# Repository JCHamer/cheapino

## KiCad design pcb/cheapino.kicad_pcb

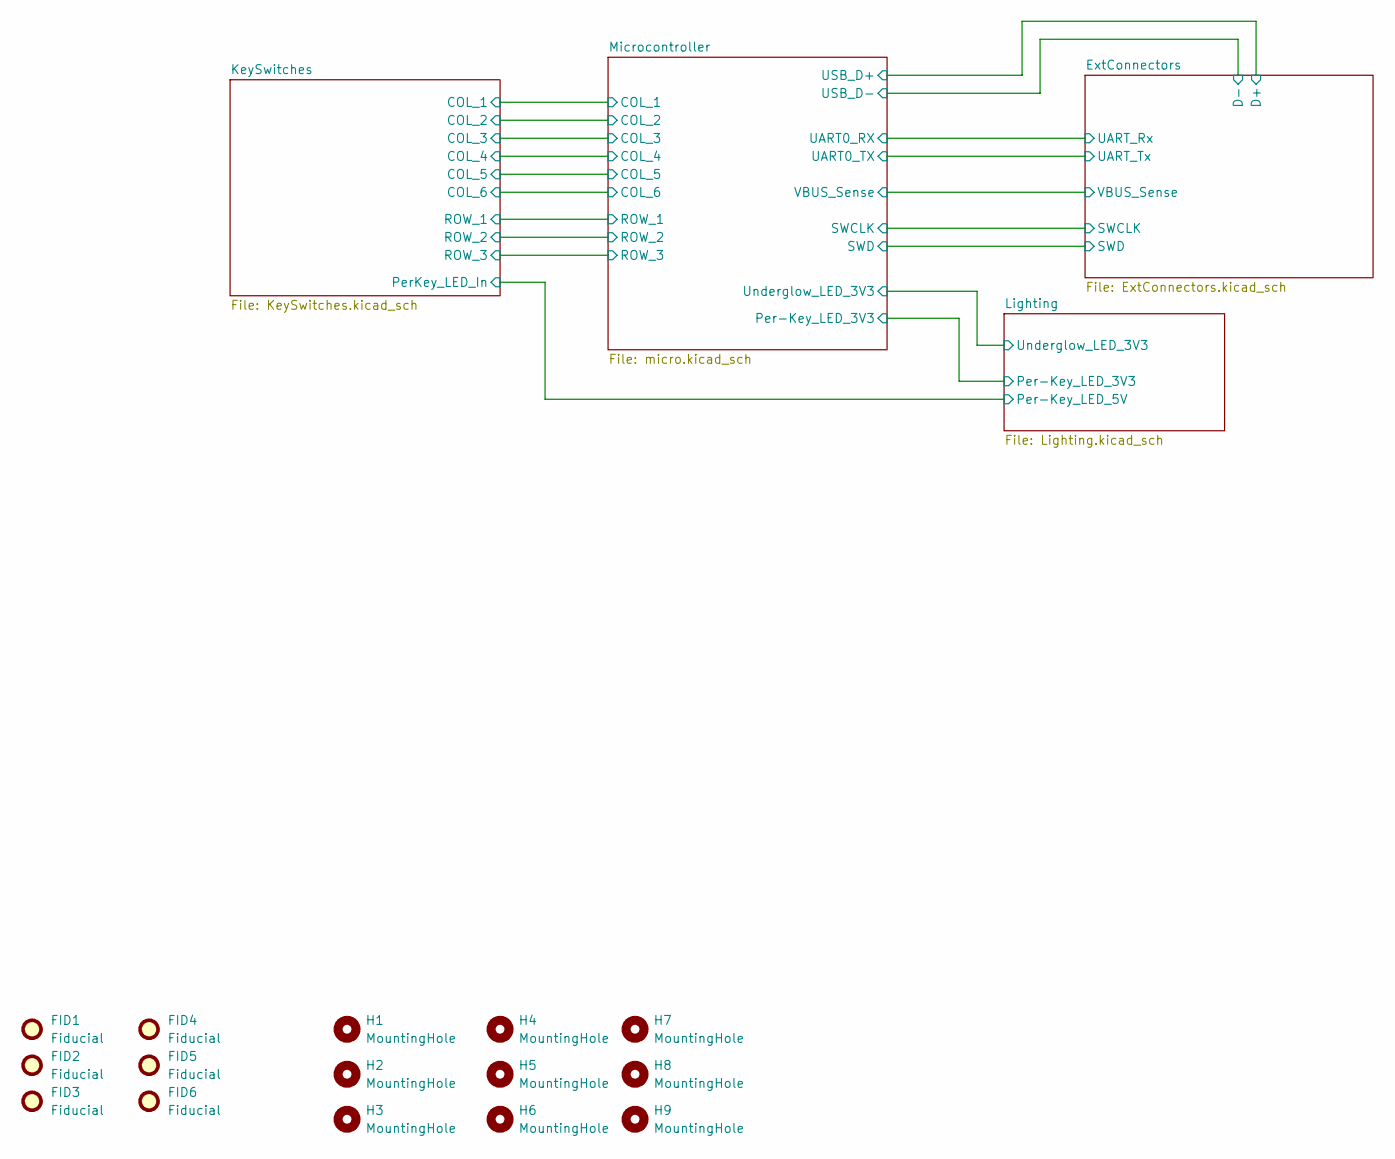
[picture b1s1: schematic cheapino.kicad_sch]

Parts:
FID1, FID2, FID3, FID4, FID5, FID6: Fiducial; Fiducial_1mm_Mask2mm
H1, H2, H3, H4, H5, H6, H7, H8, H9: MountingHole; MountingHole_2.2mm_M2

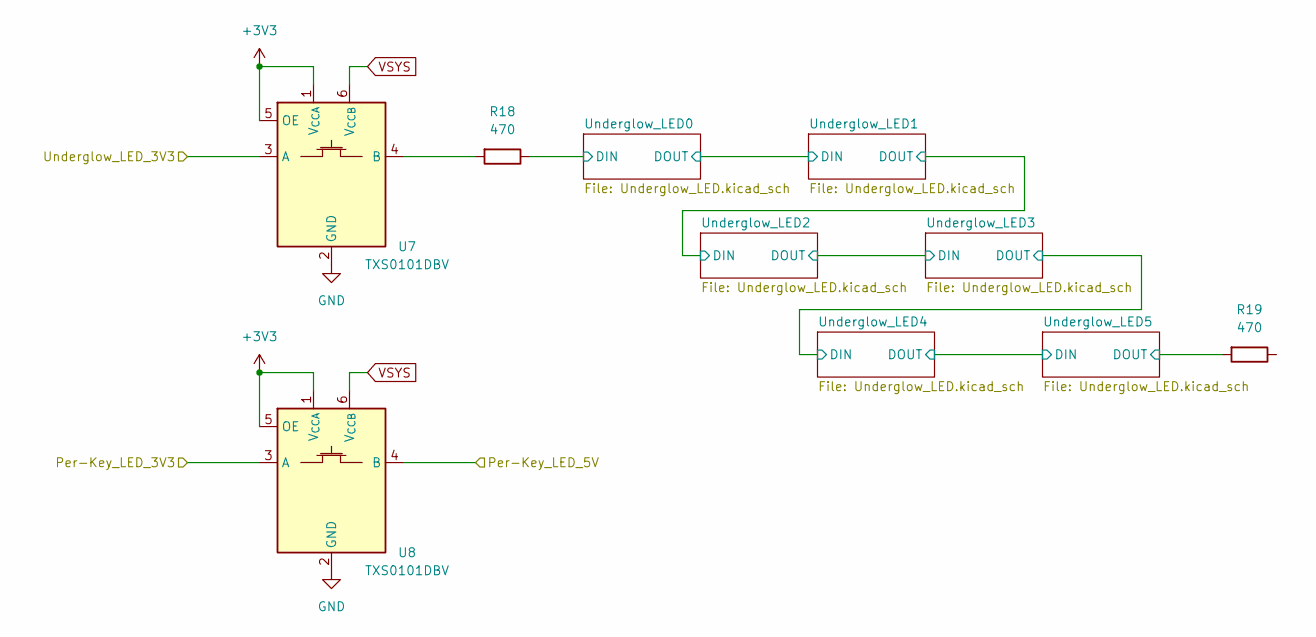
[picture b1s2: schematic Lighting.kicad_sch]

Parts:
R18, R19: 470; R_0805_2012Metric_Pad1.20x1.40mm_HandSolder
U7, U8: TXS0101DBV; SOT-23-6

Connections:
+3V3: U7.1 (V_{CCA}), U7.5 (OE), U8.1 (V_{CCA}), U8.5 (OE); also elsewhere on the board
/KeySwitches/PerKey_LED_In: U8.4 (B); also elsewhere on the board
/Lighting/Per-Key_LED_3V3: U8.3 (A); also elsewhere on the board
/Lighting/Underglow_LED0/DIN: R18.1; also elsewhere on the board
/Lighting/Underglow_LED5/DOUT: R19.2; also elsewhere on the board
/Lighting/Underglow_LED_3V3: U7.3 (A); also elsewhere on the board
GND: U7.2 (GND), U8.2 (GND); also elsewhere on the board
unnamed: R18.2, U7.4 (B)

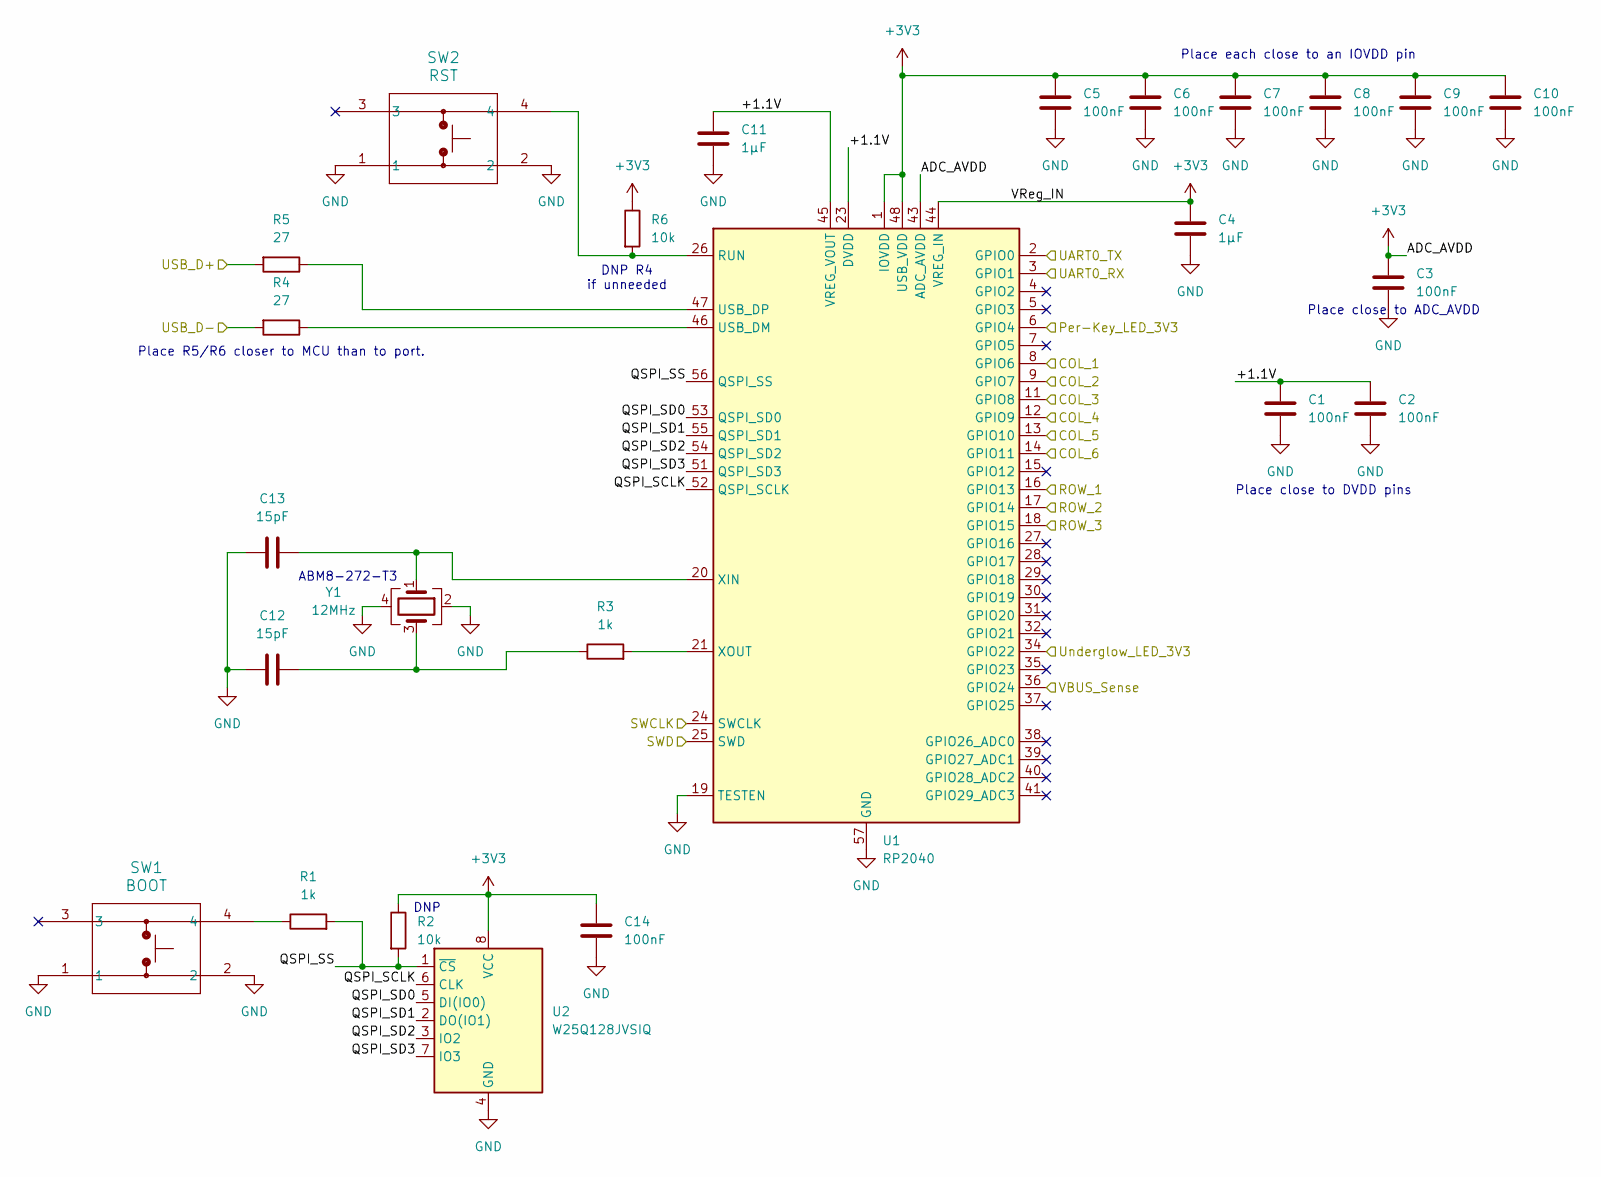
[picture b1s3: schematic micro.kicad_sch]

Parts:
C1, C2, C3, C5, C6, C7, C8, C9, C10, C14: 100nF; C_0603_1608Metric_Pad1.08x0.95mm_HandSolder
C4, C11: 1μF; C_0603_1608Metric_Pad1.08x0.95mm_HandSolder
C12, C13: 15pF; C_0603_1608Metric_Pad1.08x0.95mm_HandSolder
R1, R3: 1k; R_0603_1608Metric_Pad0.98x0.95mm_HandSolder
R2, R6: 10k; R_0603_1608Metric_Pad0.98x0.95mm_HandSolder
R4, R5: 27; R_0603_1608Metric_Pad0.98x0.95mm_HandSolder
SW1: BOOT; TL3342_EWI
SW2: RST; TL3342_EWI
U1: RP2040; QFN-56-1EP_7x7mm_P0.4mm_EP3.2x3.2mm
U2: W25Q128JVSIQ; SOIC-8_5.23x5.23mm_P1.27mm
Y1: 12MHz; ABM8272T3

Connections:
+3V3: C3.1, C4.1, C5.1, C6.1, C7.1, C8.1, C9.1, C10.1, C14.1, R2.1, R6.1, U1.1 (IOVDD), U1.10 (IOVDD), U1.22 (IOVDD), U1.33 (IOVDD), U1.42 (IOVDD), U1.43 (ADC_AVDD), U1.44 (VREG_IN), U1.48 (USB_VDD), U1.49 (IOVDD), U2.8 (VCC); also elsewhere on the board
/ExtConnectors/D+: R5.2; also elsewhere on the board
/ExtConnectors/D-: R4.2; also elsewhere on the board
/ExtConnectors/SWCLK: U1.24 (SWCLK); also elsewhere on the board
/ExtConnectors/SWD: U1.25 (SWD); also elsewhere on the board
/ExtConnectors/UART_Rx: U1.3 (GPIO1); also elsewhere on the board
/ExtConnectors/UART_Tx: U1.2 (GPIO0); also elsewhere on the board
/ExtConnectors/VBUS_Sense: U1.36 (GPIO24); also elsewhere on the board
/KeySwitches/COL_1: U1.8 (GPIO6); also elsewhere on the board
/KeySwitches/COL_2: U1.9 (GPIO7); also elsewhere on the board
/KeySwitches/COL_3: U1.11 (GPIO8); also elsewhere on the board
/KeySwitches/COL_4: U1.12 (GPIO9); also elsewhere on the board
/KeySwitches/COL_5: U1.13 (GPIO10); also elsewhere on the board
/KeySwitches/COL_6: U1.14 (GPIO11); also elsewhere on the board
/KeySwitches/ROW_1: U1.16 (GPIO13); also elsewhere on the board
/KeySwitches/ROW_2: U1.17 (GPIO14); also elsewhere on the board
/KeySwitches/ROW_3: U1.18 (GPIO15); also elsewhere on the board
/Lighting/Per-Key_LED_3V3: U1.6 (GPIO4); also elsewhere on the board
/Lighting/Underglow_LED_3V3: U1.34 (GPIO22); also elsewhere on the board
/Microcontroller/QSPI_SCLK: U1.52 (QSPI_SCLK), U2.6 (CLK)
/Microcontroller/QSPI_SD0: U1.53 (QSPI_SD0), U2.5 (DI(IO0))
/Microcontroller/QSPI_SD1: U1.55 (QSPI_SD1), U2.2 (DO(IO1))
/Microcontroller/QSPI_SD2: U1.54 (QSPI_SD2), U2.3 (IO2)
/Microcontroller/QSPI_SD3: U1.51 (QSPI_SD3), U2.7 (IO3)
/Microcontroller/QSPI_SS: R1.2, R2.2, U1.56 (QSPI_SS), U2.1 (~CS)
GND: C1.2, C2.2, C3.2, C4.2, C5.2, C6.2, C7.2, C8.2, C9.2, C10.2, C11.2, C12.1, C13.1, C14.2, SW1.1, SW1.2, SW2.1, SW2.2, U1.19 (TESTEN), U1.57 (GND), U2.4 (GND), Y1.2, Y1.4; also elsewhere on the board
unnamed: C12.2, R3.1, Y1.3
unnamed: R1.1, SW1.4
unnamed: R6.2, SW2.4, U1.26 (RUN)
unnamed: R4.1, U1.46 (USB_DM)
unnamed: R5.1, U1.47 (USB_DP)
unnamed: C13.2, U1.20 (XIN), Y1.1
unnamed: R3.2, U1.21 (XOUT)

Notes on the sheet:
Place R5/R6 closer to MCU than to port.
Place close to ADC_AVDD
DNP R4 if unneeded
ABM8-272-T3
DNP
Place each close to an IOVDD pin
Place close to DVDD pins

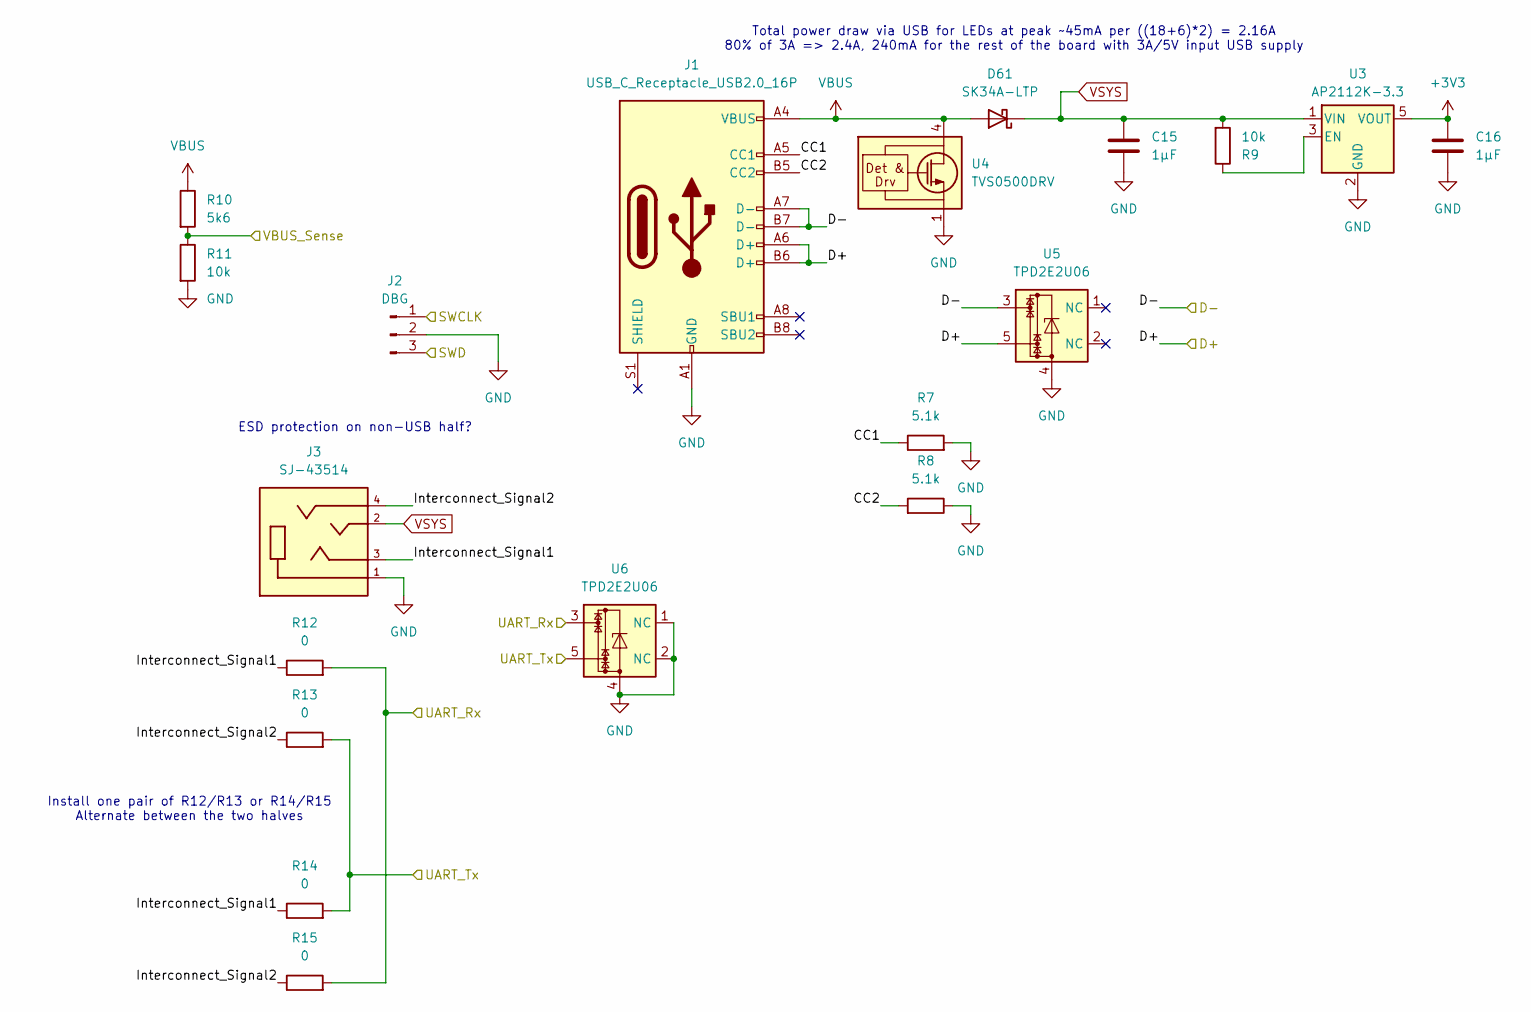
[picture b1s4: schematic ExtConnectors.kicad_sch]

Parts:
C15, C16: 1μF; C_0603_1608Metric_Pad1.08x0.95mm_HandSolder
D61: SK34A-LTP; D_SMA_Handsoldering
J1: USB_C_Receptacle_USB2.0_16P; USB_C_Receptacle_GCT_USB4105-xx-A_16P_TopMnt_Horizontal
J2: DBG; PinHeader_1x03_P2.54mm_Vertical
J3: SJ-43514; CUI_SJ-43514; PART_REV 1.04; DigiKey_Part_Number CP-43514-ND
R7, R8: 5.1k; R_0603_1608Metric_Pad0.98x0.95mm_HandSolder
R9: 10k; R_0603_1608Metric_Pad0.98x0.95mm_HandSolder
R10: 5k6; R_0805_2012Metric_Pad1.20x1.40mm_HandSolder
R11: 10k; R_0805_2012Metric_Pad1.20x1.40mm_HandSolder
R12, R13, R14, R15: 0; R_0805_2012Metric_Pad1.20x1.40mm_HandSolder
U3: AP2112K-3.3; SOT-23-5
U4: TVS0500DRV; WSON-6-1EP_2x2mm_P0.65mm_EP1x1.6mm
U5, U6: TPD2E2U06; SOT-553

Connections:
+3V3: C16.1, U3.5 (VOUT); also elsewhere on the board
/ExtConnectors/CC1: J1.A5 (CC1), R7.1
/ExtConnectors/CC2: J1.B5 (CC2), R8.2
/ExtConnectors/D+: J1.A6 (D+), J1.B6 (D+), U5.5; also elsewhere on the board
/ExtConnectors/D-: J1.A7 (D-), J1.B7 (D-), U5.3; also elsewhere on the board
/ExtConnectors/Interconnect_Signal1: J3.3, R12.1, R14.1
/ExtConnectors/Interconnect_Signal2: J3.4, R13.1, R15.1
/ExtConnectors/SWCLK: J2.1; also elsewhere on the board
/ExtConnectors/SWD: J2.3; also elsewhere on the board
/ExtConnectors/UART_Rx: R12.2, R15.2, U6.3; also elsewhere on the board
/ExtConnectors/UART_Tx: R13.2, R14.2, U6.5; also elsewhere on the board
/ExtConnectors/VBUS_Sense: R10.2, R11.1; also elsewhere on the board
GND: C15.2, C16.2, J1.A1 (GND), J1.A12 (GND), J1.B1 (GND), J1.B12 (GND), J2.2, J3.1, R7.2, R8.1, R11.2, U3.2 (GND), U4.1 (GND), U4.2 (GND), U4.3 (GND), U4.7 (GND), U5.4, U6.1 (NC), U6.2 (NC), U6.4; also elsewhere on the board
unnamed: R9.1, U3.3 (EN)
VBUS: D61.2 (A), J1.A4 (VBUS), J1.A9 (VBUS), J1.B4 (VBUS), J1.B9 (VBUS), R10.1, U4.4 (IN), U4.5 (IN), U4.6 (IN)

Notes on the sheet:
ESD protection on non-USB half?
Total power draw via USB for LEDs at peak ~45mA per ((18+6)*2) = 2.16A 80% of 3A => 2.4A, 240mA for the rest of the board with 3A/5V input USB supply
Install one pair of R12/R13 or R14/R15 Alternate between the two halves

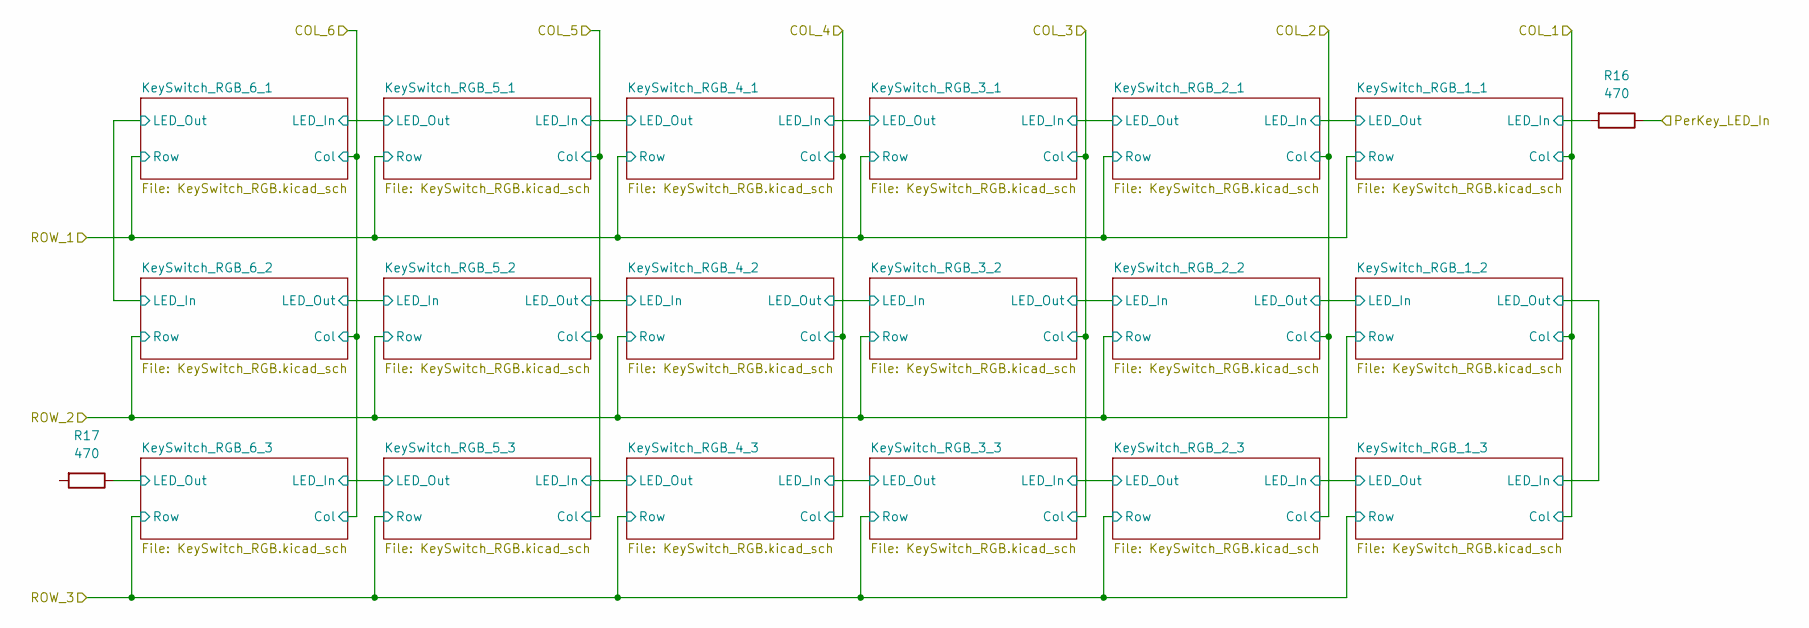
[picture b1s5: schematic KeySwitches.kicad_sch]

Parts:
R16, R17: 470; R_0805_2012Metric_Pad1.20x1.40mm_HandSolder

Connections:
/KeySwitches/KeySwitch_RGB_1_1/LED_In: R16.2; also elsewhere on the board
/KeySwitches/KeySwitch_RGB_6_3/LED_Out: R17.1; also elsewhere on the board
/KeySwitches/PerKey_LED_In: R16.1; also elsewhere on the board

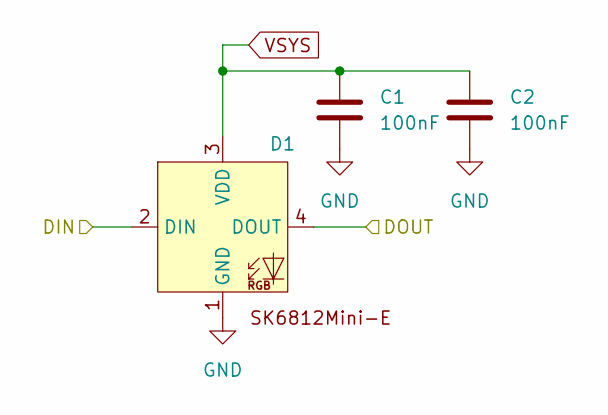
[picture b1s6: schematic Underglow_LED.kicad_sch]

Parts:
C1, C2: 100nF; C_0603_1608Metric_Pad1.08x0.95mm_HandSolder
D1: SK6812-MINI-E_ReverseMount_reversible

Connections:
/KeySwitches/KeySwitch_RGB_5_1/LED_Out: D1.2 (DIN); also elsewhere on the board
/KeySwitches/KeySwitch_RGB_6_1/LED_Out: D1.4 (DOUT); also elsewhere on the board
GND: C1.2, C2.2, D1.1 (GND); also elsewhere on the board

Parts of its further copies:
C35, C36, C37, C38, C39, C40, C59, C60, C61, C62, C63: 100nF; C_0603_1608Metric_Pad1.08x0.95mm_HandSolder
D10: SK6812-MINI-E_ReverseMount_reversible

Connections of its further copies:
/KeySwitches/KeySwitch_RGB_2_1/LED_Out: D10.2 (DIN); also elsewhere on the board
/KeySwitches/KeySwitch_RGB_3_1/LED_Out: D10.4 (DOUT); also elsewhere on the board
GND: C35.2, C36.2, C37.2, C38.2, C39.2, C40.2, C59.2, C60.2, C61.2, C62.2, C63.2, D10.1 (GND); also elsewhere on the board

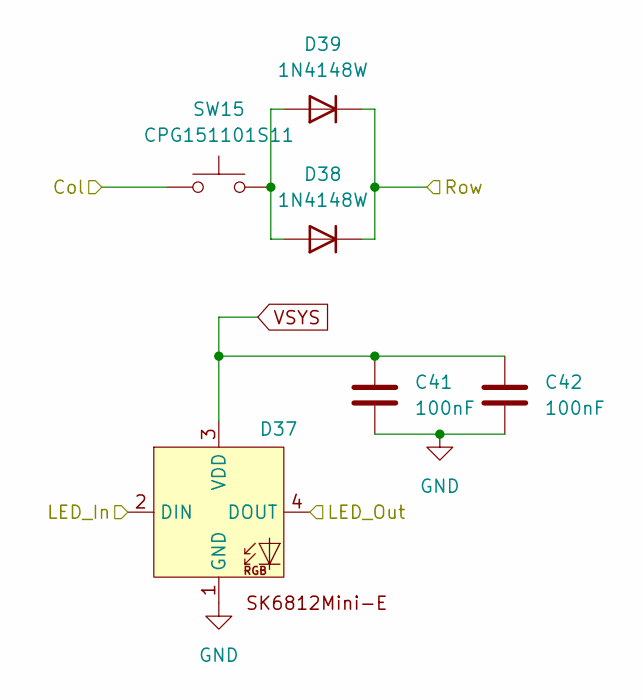
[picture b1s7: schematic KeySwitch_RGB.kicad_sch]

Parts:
C41, C42: 100nF; C_0603_1608Metric_Pad1.08x0.95mm_HandSolder
D37: SK6812-MINI-E_ReverseMount_reversible
D38, D39: 1N4148W; D_SOD-123
SW15: CPG151101S11; Kailh_socket_MX_reversible

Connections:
/KeySwitches/COL_6: SW15.1; also elsewhere on the board
/KeySwitches/KeySwitch_RGB_5_3/LED_Out: D37.2 (DIN); also elsewhere on the board
/KeySwitches/KeySwitch_RGB_6_3/LED_Out: D37.4 (DOUT); also elsewhere on the board
/KeySwitches/ROW_3: D38.1 (K), D39.1 (K); also elsewhere on the board
GND: C41.2, C42.2, D37.1 (GND); also elsewhere on the board
unnamed: D38.2 (A), D39.2 (A), SW15.2

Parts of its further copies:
C17, C18, C19, C20, C21, C22, C23, C24, C25, C26, C27, C28, C29, C30, C31, C32, C33, C34, C35, C36, C37, C38, C39, C40, C43, C44, C45, C46, C47, C48, C49, C50, C51, C52: 100nF; C_0603_1608Metric_Pad1.08x0.95mm_HandSolder
D2, D3, D5, D6, D8, D9, D11, D12, D14, D15, D17, D18, D20, D21, D23, D24, D26, D27, D29, D30, D32, D33, D35, D36, D41, D42, D44, D45, D47, D48, D50, D51, D53, D54: 1N4148W; D_SOD-123
D4, D7, D10, D13, D16, D19, D22, D25, D28, D31, D34, D40, D43, D46, D49, D52: SK6812-MINI-E_ReverseMount_reversible
SW3, SW4, SW5, SW6, SW7, SW8, SW9, SW10, SW11, SW12, SW13, SW14, SW16, SW17, SW18, SW19, SW20: CPG151101S11; Kailh_socket_MX_reversible

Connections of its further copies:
/KeySwitches/COL_1: SW8.1, SW14.1, SW20.1; also elsewhere on the board
/KeySwitches/COL_2: SW7.1, SW13.1, SW19.1; also elsewhere on the board
/KeySwitches/COL_3: SW6.1, SW12.1, SW18.1; also elsewhere on the board
/KeySwitches/COL_4: SW5.1, SW11.1, SW17.1; also elsewhere on the board
/KeySwitches/COL_5: SW4.1, SW10.1, SW16.1; also elsewhere on the board
/KeySwitches/COL_6: SW3.1, SW9.1; also elsewhere on the board
/KeySwitches/KeySwitch_RGB_1_1/LED_In: D16.2 (DIN); also elsewhere on the board
/KeySwitches/KeySwitch_RGB_1_1/LED_Out: D13.2 (DIN), D16.4 (DOUT)
/KeySwitches/KeySwitch_RGB_1_2/LED_In: D31.4 (DOUT), D34.2 (DIN)
/KeySwitches/KeySwitch_RGB_1_2/LED_Out: D34.4 (DOUT), D52.2 (DIN)
/KeySwitches/KeySwitch_RGB_1_3/LED_Out: D49.2 (DIN), D52.4 (DOUT)
/KeySwitches/KeySwitch_RGB_2_1/LED_Out: D10.2 (DIN), D13.4 (DOUT)
/KeySwitches/KeySwitch_RGB_2_2/LED_In: D28.4 (DOUT), D31.2 (DIN)
/KeySwitches/KeySwitch_RGB_2_3/LED_Out: D46.2 (DIN), D49.4 (DOUT)
/KeySwitches/KeySwitch_RGB_3_1/LED_Out: D7.2 (DIN), D10.4 (DOUT)
/KeySwitches/KeySwitch_RGB_3_2/LED_In: D25.4 (DOUT), D28.2 (DIN)
/KeySwitches/KeySwitch_RGB_3_3/LED_Out: D43.2 (DIN), D46.4 (DOUT)
/KeySwitches/KeySwitch_RGB_4_1/LED_Out: D4.2 (DIN), D7.4 (DOUT)
/KeySwitches/KeySwitch_RGB_4_2/LED_In: D22.4 (DOUT), D25.2 (DIN)
/KeySwitches/KeySwitch_RGB_4_3/LED_Out: D40.2 (DIN), D43.4 (DOUT)
/KeySwitches/KeySwitch_RGB_5_1/LED_Out: D4.4 (DOUT); also elsewhere on the board
/KeySwitches/KeySwitch_RGB_5_2/LED_In: D19.4 (DOUT), D22.2 (DIN)
/KeySwitches/KeySwitch_RGB_5_3/LED_Out: D40.4 (DOUT); also elsewhere on the board
/KeySwitches/KeySwitch_RGB_6_1/LED_Out: D19.2 (DIN); also elsewhere on the board
/KeySwitches/ROW_1: D2.1 (K), D3.1 (K), D5.1 (K), D6.1 (K), D8.1 (K), D9.1 (K), D11.1 (K), D12.1 (K), D14.1 (K), D15.1 (K), D17.1 (K), D18.1 (K); also elsewhere on the board
/KeySwitches/ROW_2: D20.1 (K), D21.1 (K), D23.1 (K), D24.1 (K), D26.1 (K), D27.1 (K), D29.1 (K), D30.1 (K), D32.1 (K), D33.1 (K), D35.1 (K), D36.1 (K); also elsewhere on the board
/KeySwitches/ROW_3: D41.1 (K), D42.1 (K), D44.1 (K), D45.1 (K), D47.1 (K), D48.1 (K), D50.1 (K), D51.1 (K), D53.1 (K), D54.1 (K); also elsewhere on the board
GND: C17.2, C18.2, C19.2, C20.2, C21.2, C22.2, C23.2, C24.2, C25.2, C26.2, C27.2, C28.2, C29.2, C30.2, C31.2, C32.2, C33.2, C34.2, C35.2, C36.2, C37.2, C38.2, C39.2, C40.2, C43.2, C44.2, C45.2, C46.2, C47.2, C48.2, C49.2, C50.2, C51.2, C52.2, D4.1 (GND), D7.1 (GND), D10.1 (GND), D13.1 (GND), D16.1 (GND), D19.1 (GND), D22.1 (GND), D25.1 (GND), D28.1 (GND), D31.1 (GND), D34.1 (GND), D40.1 (GND), D43.1 (GND), D46.1 (GND), D49.1 (GND), D52.1 (GND); also elsewhere on the board
unnamed: D2.2 (A), D3.2 (A), SW3.2
unnamed: D5.2 (A), D6.2 (A), SW4.2
unnamed: D8.2 (A), D9.2 (A), SW5.2
unnamed: D11.2 (A), D12.2 (A), SW6.2
unnamed: D14.2 (A), D15.2 (A), SW7.2
unnamed: D17.2 (A), D18.2 (A), SW8.2
unnamed: D20.2 (A), D21.2 (A), SW9.2
unnamed: D23.2 (A), D24.2 (A), SW10.2
unnamed: D26.2 (A), D27.2 (A), SW11.2
unnamed: D29.2 (A), D30.2 (A), SW12.2
unnamed: D32.2 (A), D33.2 (A), SW13.2
unnamed: D35.2 (A), D36.2 (A), SW14.2
unnamed: D41.2 (A), D42.2 (A), SW16.2
unnamed: D44.2 (A), D45.2 (A), SW17.2
unnamed: D47.2 (A), D48.2 (A), SW18.2
unnamed: D50.2 (A), D51.2 (A), SW19.2
unnamed: D53.2 (A), D54.2 (A), SW20.2

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
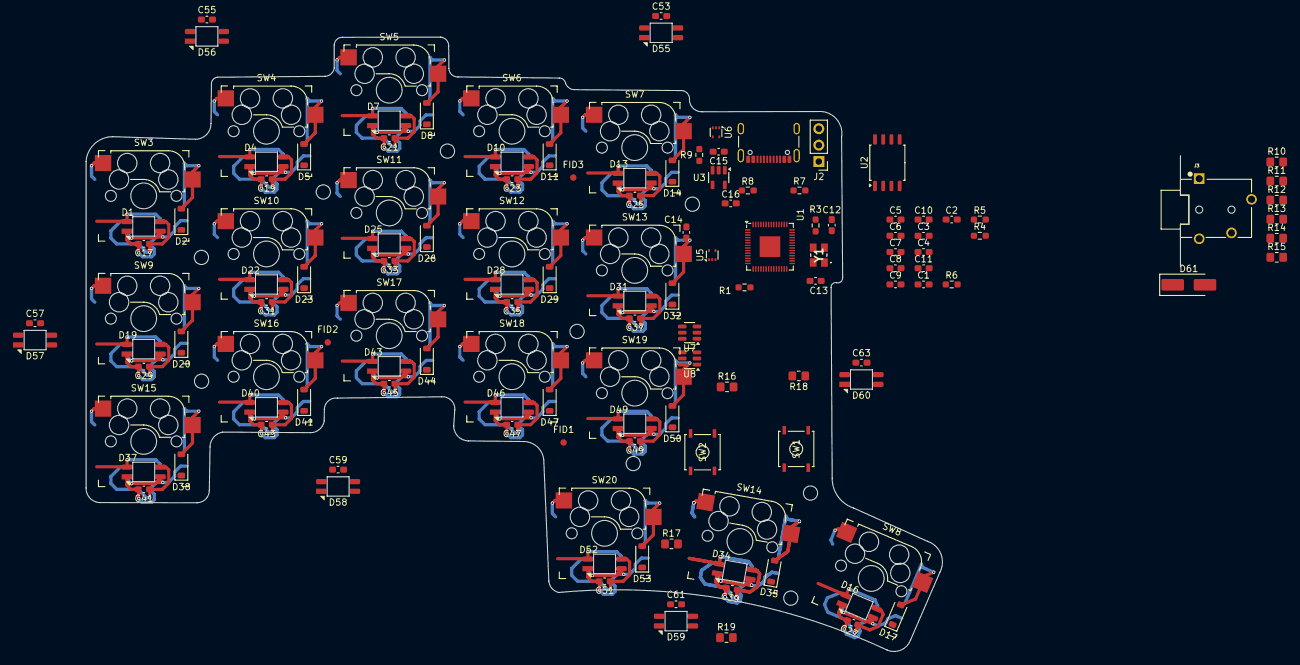
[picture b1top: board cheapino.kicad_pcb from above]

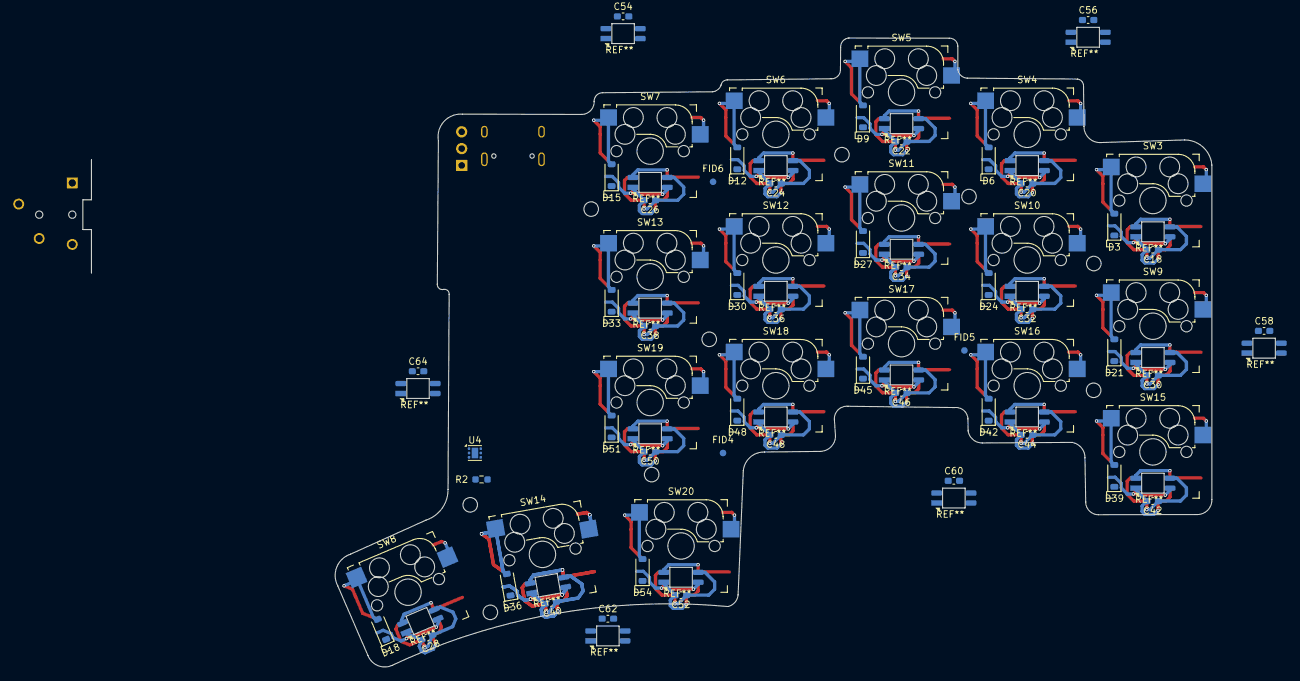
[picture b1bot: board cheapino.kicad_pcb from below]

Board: 2 copper layers, 132.5 x 95.1 mm, 191 parts (47 on the bottom side), 87 nets.

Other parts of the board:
C53, C54, C55, C56, C57, C58, C64: 100nF; C_0603_1608Metric_Pad1.08x0.95mm_HandSolder
D55, D56, D57, D58, D59, D60: SK6812-MINI-E_ReverseMount_reversible

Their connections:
/Lighting/Underglow_LED0/DIN: D55.2 (DIN); also elsewhere on the board
/Lighting/Underglow_LED0/DOUT: D55.4 (DOUT), D56.2 (DIN)
/Lighting/Underglow_LED1/DOUT: D56.4 (DOUT), D57.2 (DIN)
/Lighting/Underglow_LED2/DOUT: D57.4 (DOUT), D58.2 (DIN)
/Lighting/Underglow_LED3/DOUT: D58.4 (DOUT), D59.2 (DIN)
/Lighting/Underglow_LED4/DOUT: D59.4 (DOUT), D60.2 (DIN)
/Lighting/Underglow_LED5/DOUT: D60.4 (DOUT); also elsewhere on the board
GND: C53.2, C54.2, C55.2, C56.2, C57.2, C58.2, C64.2, D55.1 (GND), D56.1 (GND), D57.1 (GND), D58.1 (GND), D59.1 (GND), D60.1 (GND); also elsewhere on the board

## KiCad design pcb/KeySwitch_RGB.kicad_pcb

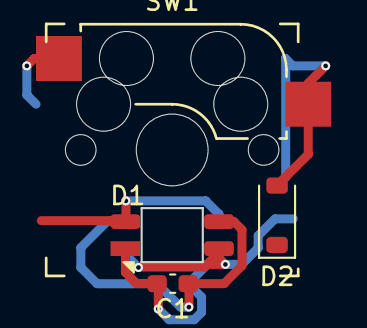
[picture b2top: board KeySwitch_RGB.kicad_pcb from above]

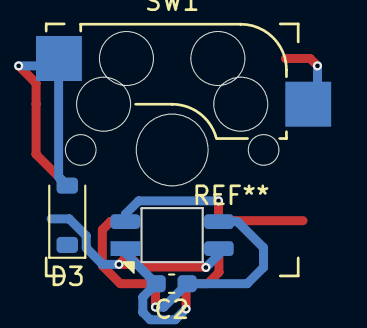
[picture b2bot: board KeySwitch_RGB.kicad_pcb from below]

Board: 2 copper layers, 6 parts (2 on the bottom side), 4 nets.

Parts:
C1, C2: 100nF; C_0603_1608Metric_Pad1.08x0.95mm_HandSolder
D1: SK6812-MINI-E_ReverseMount_reversible
D2, D3: 1N4148W; D_SOD-123
SW1: CPG151101S11; Kailh_socket_MX_reversible

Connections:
/Row: D2.1 (K), D3.1 (K)
GND: C1.2, C2.2, D1.1 (GND)
unnamed: D2.2 (A), D3.2 (A), SW1.2
VSYS: C1.1, C2.1, D1.3 (VDD)

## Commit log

2024-12-08 First pass, schematic updated for bare RP2040, SK6812-Mini RGB LED with proper series resistor and logic level shifter.
2024-12-08 First pass of applying footprints to most components.
2024-12-08 Switching from a full USB protection chip for OVP and ESD, needed for USB PD to only ESD protection. Also added chips for ESD protection for the Ethernet connectors to the other hand.
2024-12-08 Updated all footprints and libraries to match planned components.
2024-12-08 Adding jumpers to test/swap between powering SK6812 with 3.3V or 5V.
2024-12-09 Removed Rotary Encoder for space/flippability reasons and replaced all the key switch footprints that weren't bound properly to the schematic for some reason.
2024-12-09 Starting to position components and flipping passives as needed. Looking like board size is likely to need to be expanded.
2024-12-10 Placing more components onto the PCB and removing more stale leftovers from the now absent Rotary Encoder.
2025-01-11 Replacing 6 channel ESD protection with multiple 2 channel ones.
2025-01-13 WIP: Starting to migrate toward 2 independant halves.
2025-01-18 WIP: Updating keyboard matrix to use the new shared part and reorganizing all the LED outputs.
2025-01-19 Adding reversible MX Sockets and SK6812MiniE footprints, finishing the replacement of Ethernet with a TRRS connector and selectable 0Ohm resistors to swap Rx/Tx for the interconnect.
2025-01-25 Broke out Underglow LEDs into a common hierarchical sheet for what may be more consistent placements. Additionally created hierarchical PCB layouts and started using the HierarchicalPcb plugin (https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
2025-01-30 Renumbering all reference designations and adding an initial layout for each keyswtich sub-pcb.
